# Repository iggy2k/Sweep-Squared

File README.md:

# Sweep Squared
 A unibody version of the Ferris Sweep split keyboard.
 
## Why?
The only reason I gave up on using the original Sweep is being able to comfortably use it on top of the laptop keyboard. Hopefully this one will work better.
upd 06/21/2022: it does actually feel better!

## But it's just Zaphod
Yes. 

## Pics

## Firmware
https://github.com/iggy2k/zmk-squared
 
## Credits
Original Ferris is made by [pierrechevalier83](https://github.com/pierrechevalier83)

Ferris Sweep made by [davidphilipbarr](https://github.com/davidphilipbarr)

Symbols and footprints are credited below.

## Symbols and Footprints
Sources:

https://github.com/foostan/kbd

https://github.com/davidphilipbarr/Kicad-Footprints

https://github.com/ai03-2725/random-keyboard-parts.pretty

https://github.com/Biacco42/ProMicroKiCad

#### Also
ai03 pcb guide is super cool as well as ppl from the keeb discords.

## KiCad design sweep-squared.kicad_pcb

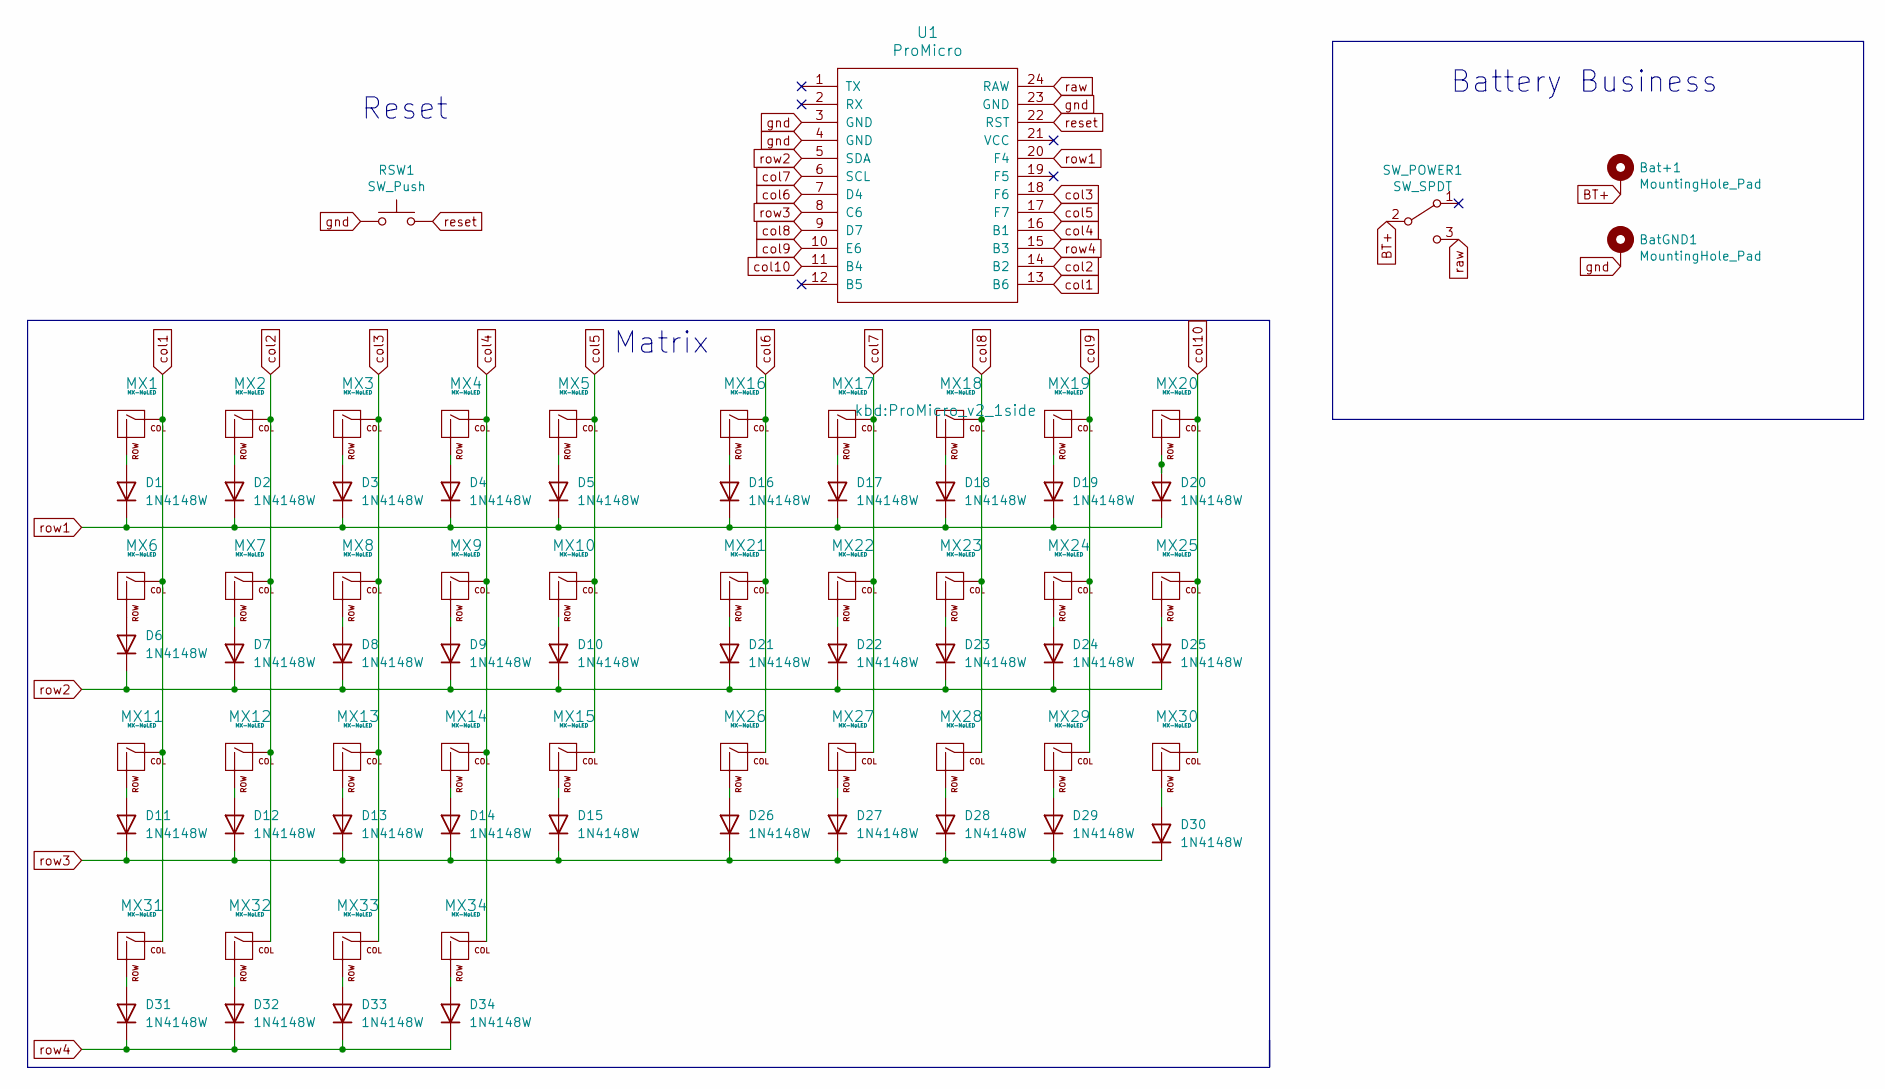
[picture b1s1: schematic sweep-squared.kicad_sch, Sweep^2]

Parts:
Bat+1: MountingHole_Pad; 1pin_conn
BatGND1: MountingHole_Pad; 1pin_conn
D1, D2, D3, D4, D5, D6, D7, D8, D9, D10, D11, D12, D13, D14, D15, D16, D17, D18, D19, D20, D21, D22, D23, D24, D25, D26, D27, D28, D29, D30, D31, D32, D33, D34: 1N4148W; D_SOD-123
MX1, MX2, MX3, MX4, MX5, MX6, MX7, MX8, MX9, MX10, MX11, MX12, MX13, MX14, MX15, MX16, MX17, MX18, MX19, MX20, MX21, MX22, MX23, MX24, MX25, MX26, MX27, MX28, MX29, MX30, MX31, MX32, MX33, MX34: MX-NoLED; SW_PG1350_single_b2
RSW1: SW_Push; ResetSW
SW_POWER1: SW_SPDT; SPDT_C128955
U1: ProMicro; ProMicro_v2_1side

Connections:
unnamed: Bat+1.1, SW_POWER1.2 (B)
unnamed: D1.2 (A), MX1.2 (ROW)
unnamed: D2.2 (A), MX2.2 (ROW)
unnamed: D3.2 (A), MX3.2 (ROW)
unnamed: D4.2 (A), MX4.2 (ROW)
unnamed: D5.2 (A), MX5.2 (ROW)
unnamed: D6.2 (A), MX6.2 (ROW)
unnamed: D7.2 (A), MX7.2 (ROW)
unnamed: D8.2 (A), MX8.2 (ROW)
unnamed: D9.2 (A), MX9.2 (ROW)
unnamed: D10.2 (A), MX10.2 (ROW)
unnamed: D11.2 (A), MX11.2 (ROW)
unnamed: D12.2 (A), MX12.2 (ROW)
unnamed: D13.2 (A), MX13.2 (ROW)
unnamed: D14.2 (A), MX14.2 (ROW)
unnamed: D15.2 (A), MX15.2 (ROW)
unnamed: D16.2 (A), MX16.2 (ROW)
unnamed: D17.2 (A), MX17.2 (ROW)
unnamed: D18.2 (A), MX18.2 (ROW)
unnamed: D19.2 (A), MX19.2 (ROW)
unnamed: D20.2 (A), MX20.2 (ROW)
unnamed: D21.2 (A), MX21.2 (ROW)
unnamed: D22.2 (A), MX22.2 (ROW)
unnamed: D23.2 (A), MX23.2 (ROW)
unnamed: D24.2 (A), MX24.2 (ROW)
unnamed: D25.2 (A), MX25.2 (ROW)
unnamed: D26.2 (A), MX26.2 (ROW)
unnamed: D27.2 (A), MX27.2 (ROW)
unnamed: D28.2 (A), MX28.2 (ROW)
unnamed: D29.2 (A), MX29.2 (ROW)
unnamed: D30.2 (A), MX30.2 (ROW)
unnamed: D31.2 (A), MX31.2 (ROW)
unnamed: D32.2 (A), MX32.2 (ROW)
unnamed: D33.2 (A), MX33.2 (ROW)
unnamed: D34.2 (A), MX34.2 (ROW)
col1: MX1.1 (COL), MX6.1 (COL), MX11.1 (COL), MX31.1 (COL), U1.13 (B6)
col2: MX2.1 (COL), MX7.1 (COL), MX12.1 (COL), MX32.1 (COL), U1.14 (B2)
col3: MX3.1 (COL), MX8.1 (COL), MX13.1 (COL), MX33.1 (COL), U1.18 (F6)
col4: MX4.1 (COL), MX9.1 (COL), MX14.1 (COL), MX34.1 (COL), U1.16 (B1)
col5: MX5.1 (COL), MX10.1 (COL), MX15.1 (COL), U1.17 (F7)
col6: MX16.1 (COL), MX21.1 (COL), MX26.1 (COL), U1.7 (D4)
col7: MX17.1 (COL), MX22.1 (COL), MX27.1 (COL), U1.6 (SCL)
col8: MX18.1 (COL), MX23.1 (COL), MX28.1 (COL), U1.9 (D7)
col9: MX19.1 (COL), MX24.1 (COL), MX29.1 (COL), U1.10 (E6)
col10: MX20.1 (COL), MX25.1 (COL), MX30.1 (COL), U1.11 (B4)
gnd: BatGND1.1, RSW1.1, U1.3 (GND), U1.4 (GND), U1.23 (GND); also elsewhere on the board
raw: SW_POWER1.3 (C), U1.24 (RAW); also elsewhere on the board
reset: RSW1.2, U1.22 (RST)
row1: D1.1 (K), D2.1 (K), D3.1 (K), D4.1 (K), D5.1 (K), D16.1 (K), D17.1 (K), D18.1 (K), D19.1 (K), D20.1 (K), U1.20 (F4)
row2: D6.1 (K), D7.1 (K), D8.1 (K), D9.1 (K), D10.1 (K), D21.1 (K), D22.1 (K), D23.1 (K), D24.1 (K), D25.1 (K), U1.5 (SDA)
row3: D11.1 (K), D12.1 (K), D13.1 (K), D14.1 (K), D15.1 (K), D26.1 (K), D27.1 (K), D28.1 (K), D29.1 (K), D30.1 (K), U1.8 (C6)
row4: D31.1 (K), D32.1 (K), D33.1 (K), D34.1 (K), U1.15 (B3)

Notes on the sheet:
Reset
Matrix
Battery Business

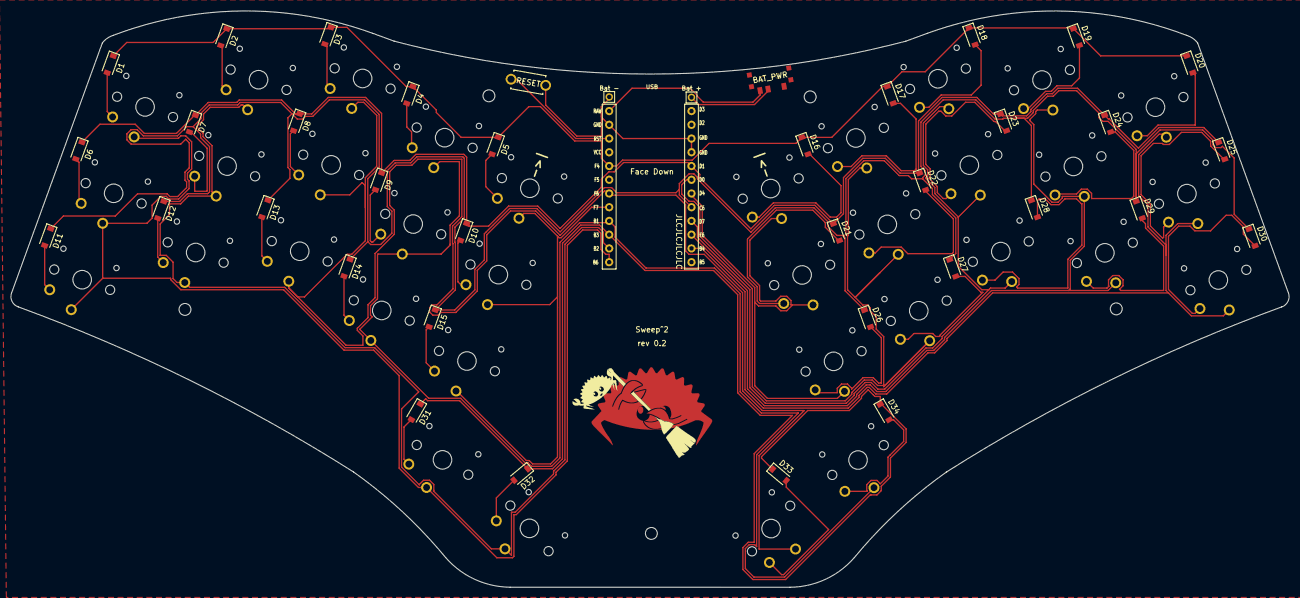
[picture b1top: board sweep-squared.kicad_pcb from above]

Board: 2 copper layers, 236.3 x 106.6 mm, 73 parts (0 on the bottom side), 52 nets.

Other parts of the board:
BAT_PWR: SW_SPDT; SPDT_C128955
Bat +: MountingHole_Pad; 1pin_conn
Bat -: MountingHole_Pad; 1pin_conn

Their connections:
BT+: BAT_PWR.2 (B), Bat +.1
gnd: Bat -.1; also elsewhere on the board
raw: BAT_PWR.3 (C); also elsewhere on the board

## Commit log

2022-06-05 Finished PCB
2022-06-05 filled readme, fixed zone, fixed logo
2022-06-06 Moved thumbkeys, tilted buttons, generated gerbers
2022-06-06 updated render
2022-06-21 Rev 0.2
    Removed questionable back silkscreen
    Fixed thumb keys position (barely visible)
    Fixed bat. switch position
    Fixed many labels
    Fixed logo
    Added 5 holes for case potential
